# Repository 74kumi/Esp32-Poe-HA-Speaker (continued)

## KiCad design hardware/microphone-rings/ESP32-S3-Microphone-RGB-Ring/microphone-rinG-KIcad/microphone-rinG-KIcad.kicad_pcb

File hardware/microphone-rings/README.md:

# Modular microphone-ring concept

## Purpose

The PoE speaker project is intended to support a family of microphone-array rings that can be adapted to many existing ceiling speakers without requiring a speaker-specific electronics design.

The concept is simple: remove the ceiling-speaker grille, choose the largest microphone ring that fits cleanly behind or within the grille, mount it around the speaker opening, route a small cable to the rear electronics, connect it to the main PoE speaker board, and reinstall the grille.

The microphone ring should be visually hidden once the grille is installed. The speaker itself remains the acoustic output device; the ring adds distributed microphones around the perimeter for room/voice capture.

This document describes the concept only. Ring PCB layouts, microphone selection, mounting methods, acoustic performance, firmware, and production dimensions are not yet validated.

## First reference speaker / Ring Rev A target

The first mechanical prototype will use a common **8-inch ceiling speaker with an approximately 9-inch (229 mm) overall grille diameter** as the reference test subject.

This reference is intentionally described by geometry rather than vendor/model. It provides a concrete starting point for the first ring while keeping the long-term goal of compatibility with many speaker families.

Initial Rev A assumptions:

| Parameter | Initial target / note |
| --- | --- |
| Nominal speaker size | 8 in |
| Measured overall grille diameter | ~9 in / 229 mm |
| Ring location | Behind the perforated grille, near the outer perimeter |
| Microphone orientation | Acoustic ports facing toward the room through the grille |
| Center opening | Keep the woofer/tweeter acoustic path substantially unobstructed |
| Microphone count | 8 target |
| Main-board interface | J4 |
| Cable routing | From ring toward rear electronics using an existing path where possible |

The **9-inch grille diameter is not the PCB diameter**. Before laying out the Rev A PCB, the grille must be removed and the actual usable inside diameter, frame lip, woofer surround clearance, grille-retention features, and available component depth measured. The PCB outside diameter should include installation clearance rather than attempting to fill the entire grille.

A practical first estimate is to target a microphone circle close to the largest clear diameter available behind the grille while keeping a narrow PCB annulus. Final OD/ID values should be based on direct measurements of the reference speaker, not the nominal 8-inch driver size.

## Design philosophy

The main PoE speaker board should remain common across installations. Speaker compatibility is handled mechanically by selecting a ring of the appropriate diameter.

Instead of making a different complete electronics system for every ceiling-speaker model, the project should eventually provide several ring diameters using the same electrical interface and microphone topology.

A useful installation should require as little modification to the existing speaker as practical:

1. Remove the speaker grille.
2. Measure the usable clear diameter behind the grille.
3. Select the largest ring variant that fits without interfering with the woofer, tweeter, grille attachment, mounting hardware, or speaker suspension.
4. Mount the ring to the grille/frame or to a small adapter using a reversible method where practical.
5. Route the ring cable toward the rear of the speaker. An existing opening is preferred. A new cable pass-through may be added only when doing so does not damage the driver, wiring, enclosure, fire rating, listing, or structural integrity of the speaker assembly.
6. Mount the PoE speaker electronics in an appropriate protected location behind/near the speaker.
7. Connect the microphone ring to the main board and reinstall the grille.

The result should look like an ordinary ceiling speaker from the room.

## Ring family

Ring sizes should be defined by geometry rather than by a specific speaker brand or model.

Each ring variant should eventually document at least:

| Parameter | Meaning |
| --- | --- |
| PCB outside diameter | Largest physical diameter of the ring PCB |
| Clear inside diameter | Opening available for the speaker cone/tweeter/acoustic path |
| Microphone-circle diameter | Diameter through the microphone acoustic ports |
| Microphone count | Intended number of microphones on the ring |
| Mounting envelope | Space needed for clips, adhesive mounts, screws, or an adapter |
| Maximum component height | Clearance required behind the grille |
| Cable exit | Location and direction of the ring cable/connector |
| Intended grille range | Approximate speaker/grille dimensions that can accept the ring |

Exact standard sizes are intentionally TBD. The first useful set should be chosen after measuring several common ceiling speakers rather than guessing from nominal woofer size alone.

A future naming scheme could use the microphone-circle or PCB outside diameter in millimeters so the name describes geometry rather than a vendor model.

## Electrical interface

The current Rev E main board reserves connector **J4** for the future microphone ring.

J4 exposes:

- 3.3 V power and grounds
- one shared `PDM_CLK`
- four PDM data signals: `PDM_DATA0_CONN` through `PDM_DATA3_CONN`
- `I2C_SDA` and `I2C_SCL`
- one spare ring GPIO

The project target is an eight-microphone ring. A likely implementation is to arrange compatible PDM microphones around the perimeter and use the four PDM data lanes for paired microphones, but the exact microphone parts, pairing method, clock rate, loading, cable constraints, connector implementation, and firmware capture scheme still require engineering validation.

The ring should not require a different main-board connector for each diameter. Electrically compatible ring sizes should be interchangeable.

## Mechanical goals

The microphone ring should:

- fit behind a perforated ceiling-speaker grille and remain visually unobtrusive;
- keep the center substantially open so it does not block the woofer or coaxial tweeter;
- avoid contact with the moving cone, surround, tweeter assembly, grille, or mounting dogs/clamps;
- tolerate speaker vibration without rattling;
- provide strain relief for its cable;
- support simple mounting methods such as clips, small standoffs, removable adhesive fixtures, or model-specific 3D-printed adapters;
- minimize required permanent modification to an existing speaker;
- allow multiple PCB diameters while keeping the same electrical design where practical.

A circular PCB is the default concept, but segmented or multi-piece rings may be considered if full circular PCBs become unnecessarily expensive at larger diameters.

## Acoustic goals and risks

The ring is intentionally close to a loudspeaker, which creates significant acoustic challenges. Mechanical fit alone is not sufficient.

Future prototypes need to evaluate:

- microphone self-noise and sensitivity through the installed grille;
- consistency between microphone positions;
- vibration mechanically coupled from the speaker/frame into the microphones;
- airflow and pressure effects near the woofer;
- acoustic shadowing caused by the speaker frame or grille structure;
- microphone saturation while the local speaker is playing;
- echo cancellation / speaker-reference requirements for simultaneous playback and voice capture;
- beamforming performance at different ring diameters;
- whether microphone spacing creates useful or harmful spatial aliasing over the intended voice band.

Ring diameter should therefore be treated as an acoustic parameter as well as a mechanical one.

## Installation and safety constraints

The goal is broad retrofit compatibility, not permission to modify every speaker indiscriminately.

Do not drill or modify a speaker assembly when doing so would compromise a listed backcan, fire/plenum rating, transformer enclosure, mains/high-voltage wiring, structural mounting, warranty, or other required safety feature. When an existing cable path is available, use it.

The microphone ring and main electronics also need an installation method that cannot fall into the occupied space if a grille or adhesive mount fails.

## Proposed development sequence

1. Fully measure the 8-inch / ~9-inch-grille reference speaker: usable grille ID, frame lip, clear ring area, depth, grille-retention features, obstructions, and cable-routing options.
2. Use those measurements to define Ring Rev A OD, ID, microphone-circle diameter, board width, component-height limit, mounting points, and cable exit.
3. Select and electrically validate the PDM microphone topology against J4.
4. Build Ring Rev A and prove microphone capture before producing every mechanical size.
5. Evaluate mounting approaches behind the reference grille.
6. Test microphone response with the local speaker silent and playing.
7. Evaluate beamforming / direction finding / voice capture and echo-cancellation requirements.
8. Measure several other common ceiling speakers and choose additional ring diameters that cover meaningfully different geometries.
9. Once the electrical design is stable, replicate the same circuit topology into those additional ring diameters.

## Relationship to the main board

The microphone ring is a separate future PCB from the Rev E PoE speaker main board. Development of the ring should not block first-prototype validation of Ethernet, power, DAC, and amplifier functions on the main board.

The current J4 interface is a design provision, not proof that an eight-microphone capture system is complete or validated.

## Archived six-microphone RGB ring handoff

The supplied ESP32-S3 six-microphone / RGB ring PCB package is archived at [`ESP32-S3-Microphone-RGB-Ring/`](ESP32-S3-Microphone-RGB-Ring/). The user reports that this design was reviewed and verified by an engineer. The archive includes KiCad sources, manufacturing outputs, BOM, placement data, STEP, reports, design notes, and component datasheets. The package is preserved as supplied; final production work should use the verified engineer handoff and the numbered J4 connector guide rather than assumptions based on connector orientation.

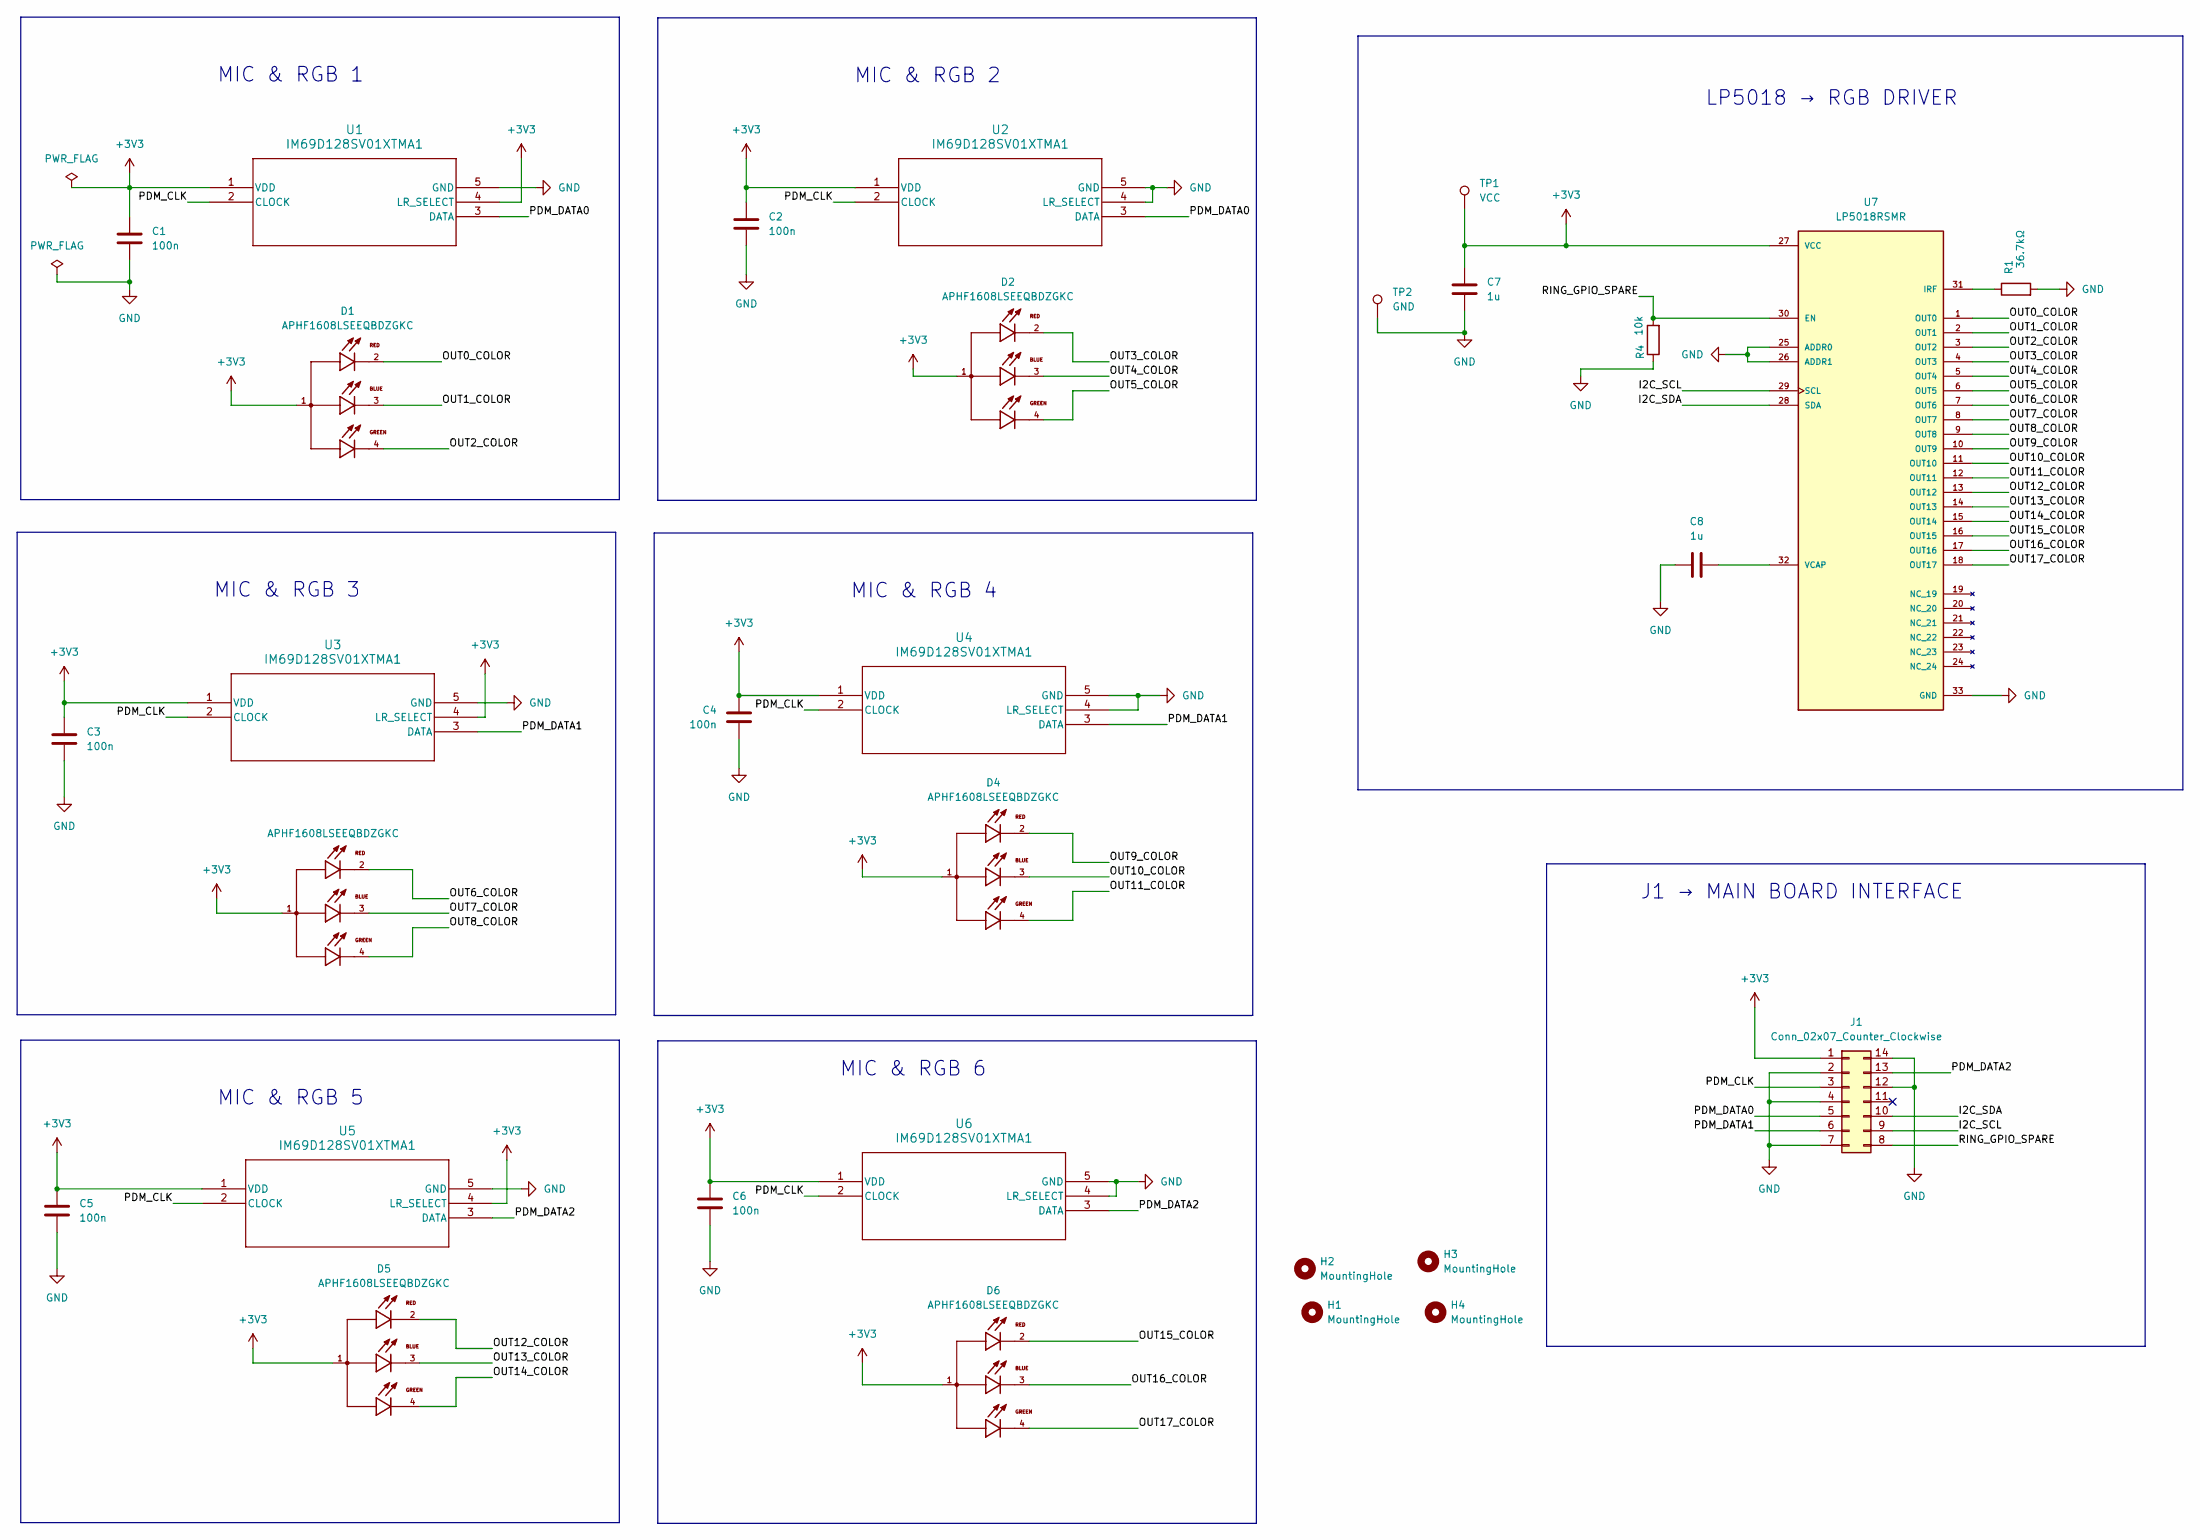
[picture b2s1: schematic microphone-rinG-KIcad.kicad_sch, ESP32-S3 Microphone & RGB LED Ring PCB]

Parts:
C1, C2, C3, C4, C5, C6: 100n; C_0402_1005Metric
C7, C8: 1u; C_0402_1005Metric
D1, D2, D3, D4, D5, D6: APHF1608LSEEQBDZGKC; LED_APHF1608LSEEQBDZGKC; PARTREV V.6B
H1, H2, H3, H4: MountingHole; MountingHole_3.2mm_M3
J1: Conn_02x07_Counter_Clockwise; PinSocket_2x07_P2.54mm_Vertical
R1: 36.7kΩ; R_0402_1005Metric
R4: 10k; R_0402_1005Metric
TP1: VCC; TestPoint_Pad_D1.5mm
TP2: GND; TestPoint_Pad_D1.5mm
U1, U2, U3, U4, U5, U6: IM69D128SV01XTMA1; MIC-SMD_IM69D128SV01XTMA1
U7: LP5018RSMR; QFN40P400X400X100-33N; PARTREV 4219108/B 08/2019

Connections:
+3V3: C1.1, C2.1, C3.1, C4.1, C5.1, C6.1, C7.1, D1.1, D2.1, D3.1, D4.1, D5.1, D6.1, J1.1, TP1.1 (1_1), U1.1 (VDD), U1.4 (LR_SELECT), U2.1 (VDD), U3.1 (VDD), U3.4 (LR_SELECT), U4.1 (VDD), U5.1 (VDD), U5.4 (LR_SELECT), U6.1 (VDD), U7.27 (VCC)
/I2C_SCL: J1.9, U7.29 (SCL)
/I2C_SDA: J1.10, U7.28 (SDA)
/OUT0_COLOR: D1.2, U7.1 (OUT0)
/OUT1_COLOR: D1.3, U7.2 (OUT1)
/OUT2_COLOR: D1.4, U7.3 (OUT2)
/OUT3_COLOR: D2.2, U7.4 (OUT3)
/OUT4_COLOR: D2.3, U7.5 (OUT4)
/OUT5_COLOR: D2.4, U7.6 (OUT5)
/OUT6_COLOR: D3.2, U7.7 (OUT6)
/OUT7_COLOR: D3.3, U7.8 (OUT7)
/OUT8_COLOR: D3.4, U7.9 (OUT8)
/OUT9_COLOR: D4.2, U7.10 (OUT9)
/OUT10_COLOR: D4.3, U7.11 (OUT10)
/OUT11_COLOR: D4.4, U7.12 (OUT11)
/OUT12_COLOR: D5.2, U7.13 (OUT12)
/OUT13_COLOR: D5.3, U7.14 (OUT13)
/OUT14_COLOR: D5.4, U7.15 (OUT14)
/OUT15_COLOR: D6.2, U7.16 (OUT15)
/OUT16_COLOR: D6.3, U7.17 (OUT16)
/OUT17_COLOR: D6.4, U7.18 (OUT17)
/PDM_CLK: J1.3, U1.2 (CLOCK), U2.2 (CLOCK), U3.2 (CLOCK), U4.2 (CLOCK), U5.2 (CLOCK), U6.2 (CLOCK)
/PDM_DATA0: J1.5, U1.3 (DATA), U2.3 (DATA)
/PDM_DATA1: J1.6, U3.3 (DATA), U4.3 (DATA)
/PDM_DATA2: J1.13, U5.3 (DATA), U6.3 (DATA)
/RING_GPIO_SPARE: J1.8, R4.2, U7.30 (EN)
GND: C1.2, C2.2, C3.2, C4.2, C5.2, C6.2, C7.2, C8.1, J1.2, J1.4, J1.7, J1.12, J1.14, R1.2, R4.1, TP2.1 (1_1), U1.5 (GND), U2.4 (LR_SELECT), U2.5 (GND), U3.5 (GND), U4.4 (LR_SELECT), U4.5 (GND), U5.5 (GND), U6.4 (LR_SELECT), U6.5 (GND), U7.25 (ADDR0), U7.26 (ADDR1), U7.33 (GND), U7.34 (GND), U7.35 (GND), U7.36 (GND), U7.37 (GND), U7.38 (GND)
unnamed: R1.1, U7.31 (IRF)
unnamed: C8.2, U7.32 (VCAP)

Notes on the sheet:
MIC & RGB 6
J1 → MAIN BOARD INTERFACE
MIC & RGB 1
LP5018 → RGB DRIVER
MIC & RGB 3
MIC & RGB 5
MIC & RGB 4
MIC & RGB 2

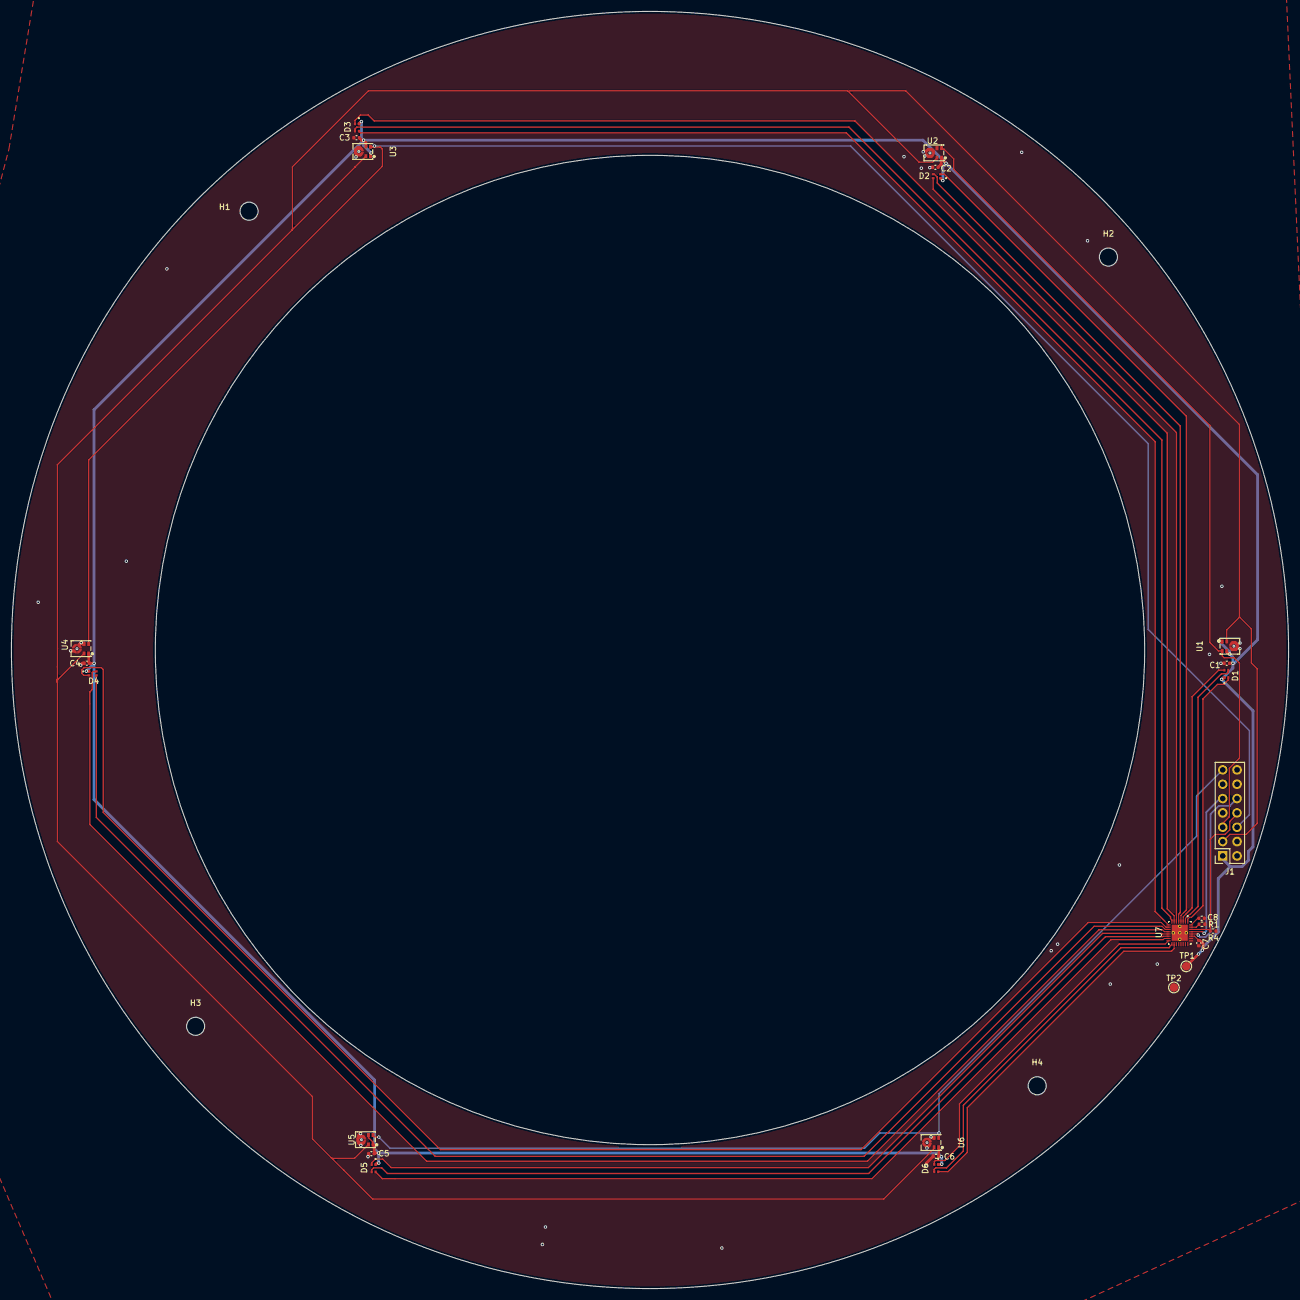
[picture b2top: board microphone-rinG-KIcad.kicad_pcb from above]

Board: 2 copper layers, 226.3 x 226.3 mm, 30 parts (0 on the bottom side), 29 nets.

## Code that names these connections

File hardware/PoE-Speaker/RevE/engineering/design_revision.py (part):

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# Module pin numbers, not GPIO numbers. Avoid Octal PSRAM GPIO35/36/37.
s3={1:'GND',2:'3V3',3:'ESP_EN',4:'PDM_CLK_MCU',5:'PDM_DATA0',6:'PDM_DATA1',7:'PDM_DATA2',12:'PDM_DATA3',
    17:'I2S_BCLK',18:'I2S_LRCLK',19:'I2S_DATA',20:'ETH_SPI_SCLK_MCU',21:'ETH_SPI_MOSI_MCU',22:'ETH_SPI_MISO',
    8:'ETH_SPI_CS_N',9:'ETH_INT_N',11:'I2C_SDA',23:'I2C_SCL',39:'RING_GPIO_SPARE',38:'IOX_INT_N',
    31:'IOX_nRESET',27:'BOOT_GPIO0',36:'UART0_RX',37:'UART0_TX',40:'GND',41:'GND'}
for p,n in s3.items():connect('U2',p,n)
# Hardware-mode/reset interface remains on the existing GPIO expander.
connect('U11',1,'IOX_INT_N')
for ref,c in components.items():
    if ref=='U2':continue
    for p in c['pins']:
        if p['net']=='RMII_REF_CLK':p['net']='BOOT_GPIO0' # SW2/J5 boot access
        elif p['net']=='RMII_REF_CLK_SRC':p['net']=None
        elif p['net']=='RMII_CLK_EN':p['net']=None

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resistor('R108','33','ETH_SPI_SCLK_MCU','ETH_SPI_SCLK',(132,74))
resistor('R109','33','ETH_SPI_MOSI_MCU','ETH_SPI_MOSI',(132,77))
# 25 MHz LVCMOS oscillator permits a grounded supply and a simple four-pad footprint.
add('X2','25MHz',{'1':'3V3','2':'GND','3':'ETH_25MHZ','4':'3V3'},'Oscillator:Oscillator_SMD_Abracon_ASE-4Pin_3.2x2.5mm','Ethernet',(125,81),'ASE-25.000MHZ-LC-T')
capacitor('C115','100nF','3V3','GND',(130,81))
resistor('R110','10k','3V3','BOOT_GPIO0',(135,55),'Controller')
resistor('R111','10k','3V3','IOX_INT_N',(152,76),'Controller')
# Keep strapping GPIO3/45/46 unused. Their default pulls/eFuse settings are authoritative.
changes.append({'change':'GPIO allocation and native four-line PDM RX moved to ESP32-S3','pin_map':s3})
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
